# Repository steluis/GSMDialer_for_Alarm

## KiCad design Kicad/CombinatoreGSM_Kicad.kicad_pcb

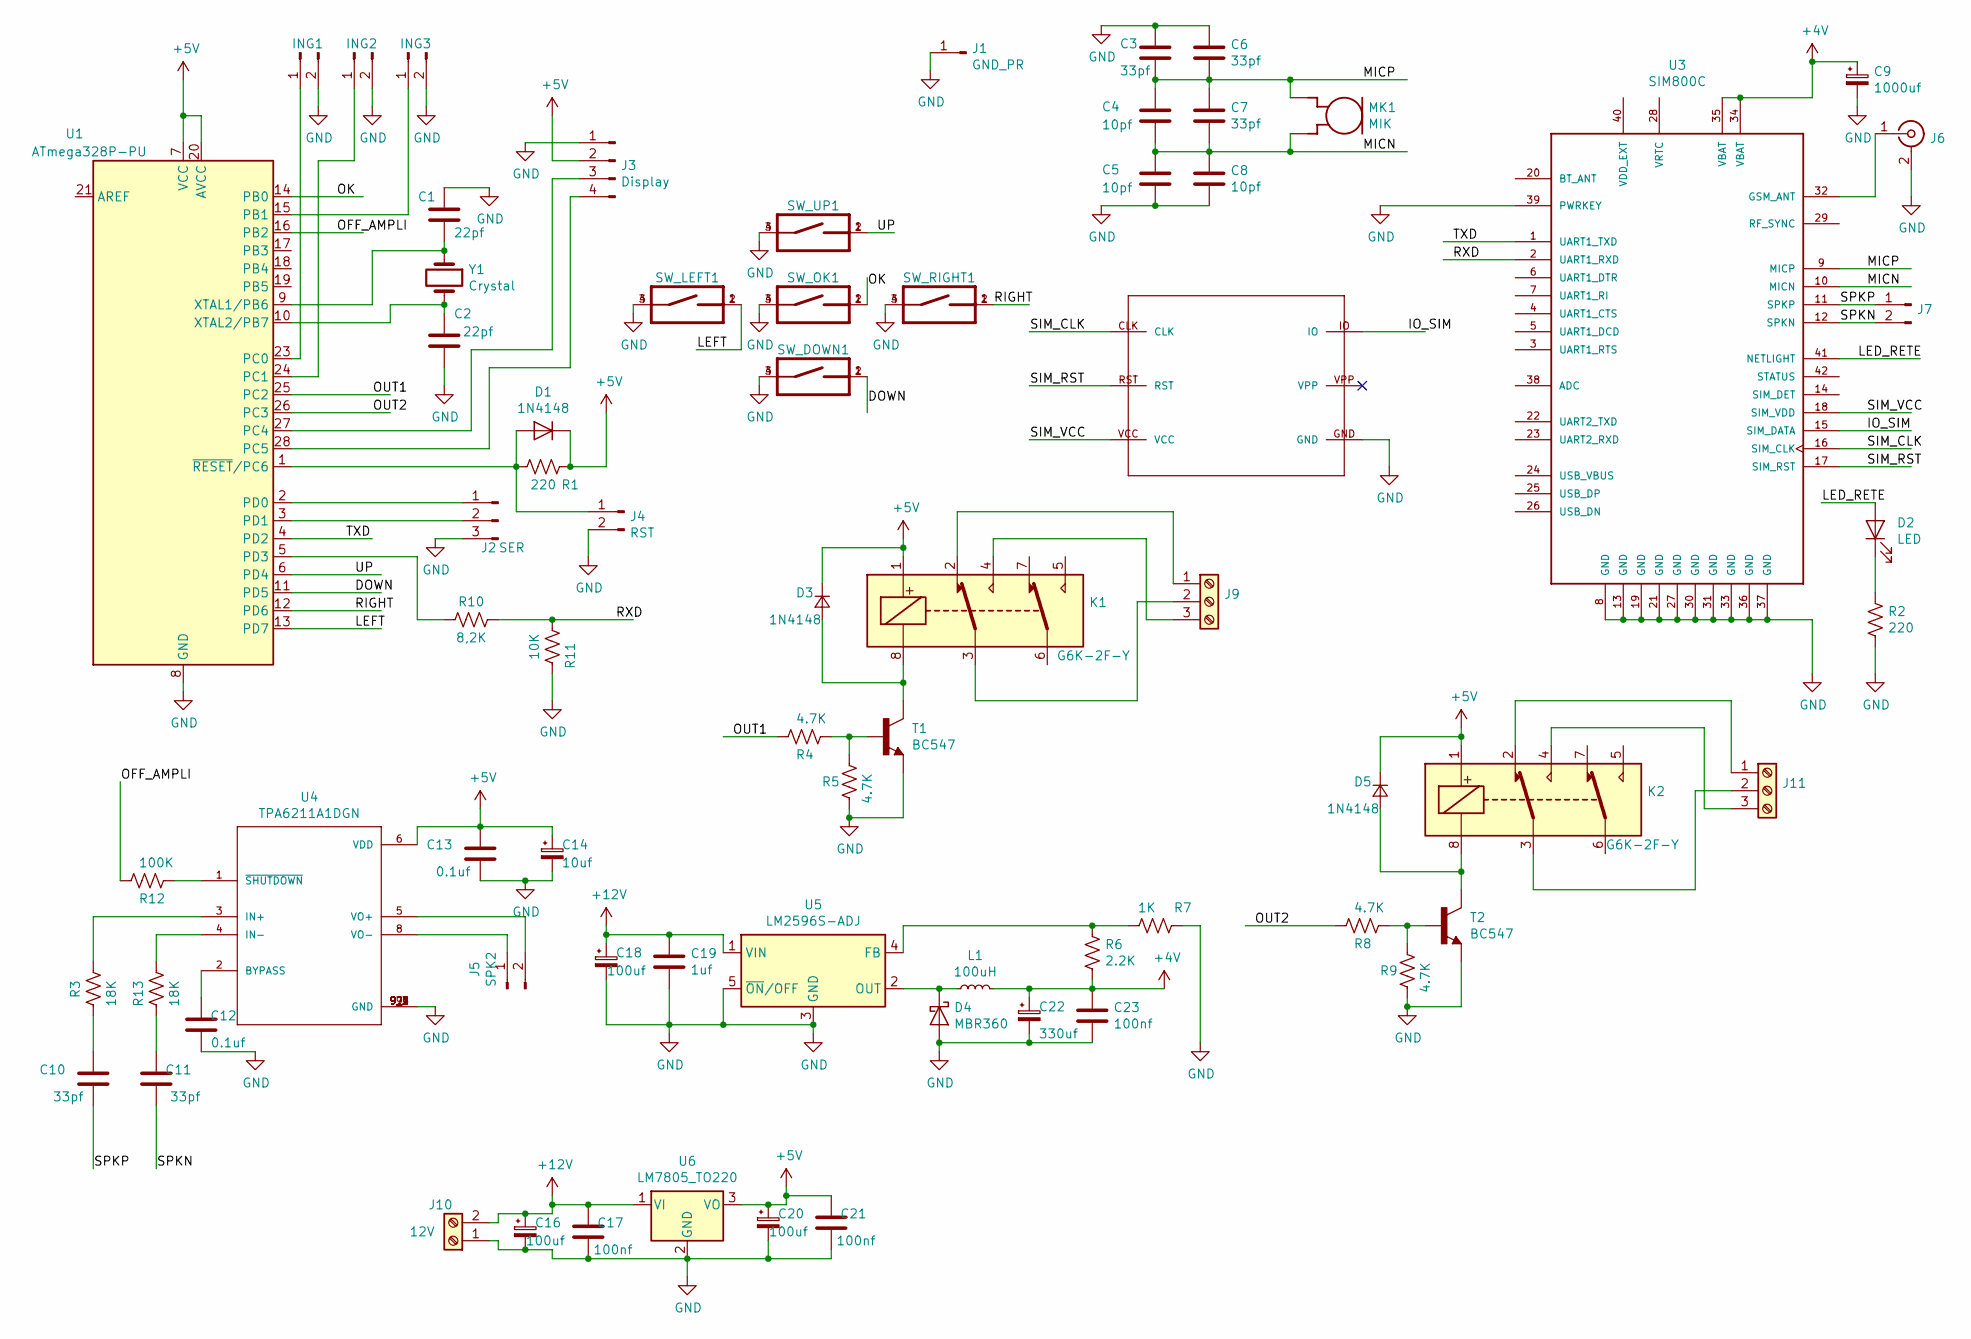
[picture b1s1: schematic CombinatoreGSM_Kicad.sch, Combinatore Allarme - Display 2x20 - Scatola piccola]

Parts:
C1, C2: 22pf; C_Disc_D3.0mm_W1.6mm_P2.50mm
C3, C6, C7, C10, C11: 33pf; C_0805_2012Metric_Pad1.15x1.40mm_HandSolder
C4, C5, C8: 10pf; C_0805_2012Metric_Pad1.15x1.40mm_HandSolder
C9: 1000uf; CP_Elec_10x10
C12, C13: 0.1uf; C_0805_2012Metric_Pad1.15x1.40mm_HandSolder
C14: 10uf; CP_Elec_6.3x5.9
C16, C18, C20: 100uf; CP_Elec_6.3x5.9
C17, C21, C23: 100nf; C_0805_2012Metric_Pad1.15x1.40mm_HandSolder
C19: 1uf; C_0805_2012Metric_Pad1.15x1.40mm_HandSolder
C22: 330uf; CP_Elec_6.3x5.9
D1, D3, D5: 1N4148; D_SOD-123
D2: LED; LED_D3.0mm
D4: MBR360; D_2010_5025Metric
ING1, ING2, ING3: TerminalBlock_4Ucon_1x02_P3.50mm_Horizontal
J1: GND_PR; PinHeader_1x01_P2.54mm_Vertical
J2: SER; PinHeader_1x03_P2.54mm_Vertical
J3: Display; PinHeader_1x04_P2.54mm_Horizontal
J4: RST; PinHeader_1x02_P2.54mm_Vertical
J5: SPK2; PinHeader_1x02_P2.54mm_Vertical
J6: U.FL_Hirose_U.FL-R-SMT-1_Vertical
J7: PinHeader_1x02_P2.54mm_Vertical
J9, J11: TerminalBlock_4Ucon_1x03_P3.50mm_Horizontal
J10: 12V; TerminalBlock_4Ucon_1x02_P3.50mm_Horizontal
K1, K2: G6K-2F-Y; Relay_DPDT_Omron_G6K-2F-Y
L1: 100uH; L_Axial_L7.0mm_D3.3mm_P12.70mm_Horizontal_Fastron_MICC
MK1: MIK; CUI_CMA-6542PF
R1, R2: 220; R_0805_2012Metric
R3, R13: 18K; R_0805_2012Metric
R4, R5, R8, R9: 4.7K; R_0805_2012Metric
R6: 2.2K; R_0805_2012Metric
R7: 1K; R_0805_2012Metric
R10: 8,2K; R_0805_2012Metric
R11: 10K; R_0805_2012Metric
R12: 100K; R_0805_2012Metric
SW_DOWN1: PULSANTE_DIP_SWITCH
SW_LEFT1: PULSANTE_DIP_SWITCH
SW_OK1: PULSANTE_DIP_SWITCH
SW_RIGHT1: PULSANTE_DIP_SWITCH
SW_UP1: PULSANTE_DIP_SWITCH
T1, T2: BC547; TO92
U1: ATmega328P-PU; DIP-28_W7.62mm
U2: NANO_SIM_CARD_HOLDER
U3: SIM800C; LCC110P1570X1760X250-42N
U4: TPA6211A1DGN; SOP65P490X110-9N
U5: LM2596S-ADJ; TO-263-5_TabPin3
U6: LM7805_TO220; TO-220-3_Horizontal_TabDown
Y1: Crystal; Crystal_HC49-4H_Vertical

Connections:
+4V: C9.1, C22.1, C23.1, L1.2, R6.2, U3.34 (VBAT), U3.35 (VBAT)
+5V: C13.2, C14.1, C20.1, C21.2, D1.1 (K), D3.1 (K), D5.1 (K), J3.2, K1.1, K2.1, R1.1, U1.7 (VCC), U1.20 (AVCC), U4.6 (VDD), U6.3 (VO); also elsewhere on the board
+12V: C16.1, C17.2, C18.1, C19.1, J10.2, U5.1 (VIN), U6.1 (VI)
/DOWN: SW_DOWN1.1 (2), SW_DOWN1.2, U1.11 (PD5)
/IO_SIM: U2.IO, U3.15 (SIM_DATA)
/LED_RETE: D2.2 (A), U3.41 (NETLIGHT)
/LEFT: SW_LEFT1.1 (2), SW_LEFT1.2, U1.13 (PD7)
/MICN: C4.2, C5.1, C7.2, C8.1, MK1.OUT, U3.10 (MICN)
/MICP: C3.2, C4.1, C6.2, C7.1, MK1.GND, U3.9 (MICP)
/OFF_AMPLI: R12.2, U1.16 (PB2)
/OK: SW_OK1.1 (2), SW_OK1.2, U1.14 (PB0)
/OUT1: R4.2, U1.25 (PC2)
/OUT2: R8.2, U1.26 (PC3)
/RIGHT: SW_RIGHT1.1 (2), SW_RIGHT1.2, U1.12 (PD6)
/RXD: R10.1, R11.2, U3.2 (UART1_RXD)
/SIM_CLK: U2.CLK, U3.16 (SIM_CLK)
/SIM_RST: U2.RST, U3.17 (SIM_RST)
/SIM_VCC: U2.VCC, U3.18 (SIM_VDD)
/SPKN: C11.1, J7.2, U3.12 (SPKN)
/SPKP: C10.1, J7.1, U3.11 (SPKP)
/TXD: U1.4 (PD2), U3.1 (UART1_TXD)
/UP: SW_UP1.1 (2), SW_UP1.2, U1.6 (PD4)
GND: C1.1, C2.2, C3.1, C5.2, C6.1, C8.2, C9.2, C12.1, C13.1, C14.2, C16.2, C17.1, C18.2, C19.2, C20.2, C21.1, C22.2, C23.2, D4.2 (A), ING1.2, ING2.2, ING3.2, J1.1, J2.3, J3.1, J4.2, J6.2 (Ext), J10.1, R2.2, R5.1, R7.1, R9.1, R11.1, SW_DOWN1.3 (1), SW_DOWN1.4 (1), SW_LEFT1.3 (1), SW_LEFT1.4 (1), SW_OK1.3 (1), SW_OK1.4 (1), SW_RIGHT1.3 (1), SW_RIGHT1.4 (1), SW_UP1.3 (1), SW_UP1.4 (1), T1.1 (E), T2.1 (E), U1.8 (GND), U1.22 (GND), U2.GND, U3.8 (GND), U3.13 (GND), U3.19 (GND), U3.21 (GND), U3.27 (GND), U3.30 (GND), U3.31 (GND), U3.33 (GND), U3.36 (GND), U3.37 (GND), U3.39 (PWRKEY), U4.7 (GND), U4.9 (GND), U4.9_1 (GND), U4.9_2 (GND), U4.9_3 (GND), U4.9_4 (GND), U4.9_5 (GND), U5.3 (GND), U5.5 (~ON~/OFF), U6.2 (GND); also elsewhere on the board
unnamed: C1.2, U1.9 (XTAL1/PB6), Y1.1
unnamed: C2.1, U1.10 (XTAL2/PB7), Y1.2
unnamed: C10.2, R3.1
unnamed: C11.2, R13.1
unnamed: C12.2, U4.2 (BYPASS)
unnamed: D1.2 (A), J4.1, R1.2, U1.1 (~RESET~/PC6)
unnamed: D2.1 (K), R2.1
unnamed: D3.2 (A), K1.8, T1.3 (C)
unnamed: D4.1 (K), L1.1, U5.2 (OUT)
unnamed: D5.2 (A), K2.8, T2.3 (C)
unnamed: ING1.1, U1.23 (PC0)
unnamed: ING2.1, U1.24 (PC1)
unnamed: ING3.1, U1.15 (PB1)
unnamed: J2.1, U1.2 (PD0)
unnamed: J2.2, U1.3 (PD1)
unnamed: J3.3, U1.27 (PC4)
unnamed: J3.4, U1.28 (PC5)
unnamed: J5.1, U4.8 (VO-)
unnamed: J5.2, U4.5 (VO+)
unnamed: J6.1 (In), U3.32 (GSM_ANT)
unnamed: J9.1, K1.2
unnamed: J9.2, K1.3
unnamed: J9.3, K1.4
unnamed: J11.1, K2.2
unnamed: J11.2, K2.3
unnamed: J11.3, K2.4
unnamed: R3.2, U4.3 (IN+)
unnamed: R4.1, R5.2, T1.2 (B)
unnamed: R6.1, R7.2, U5.4 (FB)
unnamed: R8.1, R9.2, T2.2 (B)
unnamed: R10.2, U1.5 (PD3)
unnamed: R12.1, U4.1 (~SHUTDOWN~)
unnamed: R13.2, U4.4 (IN-)

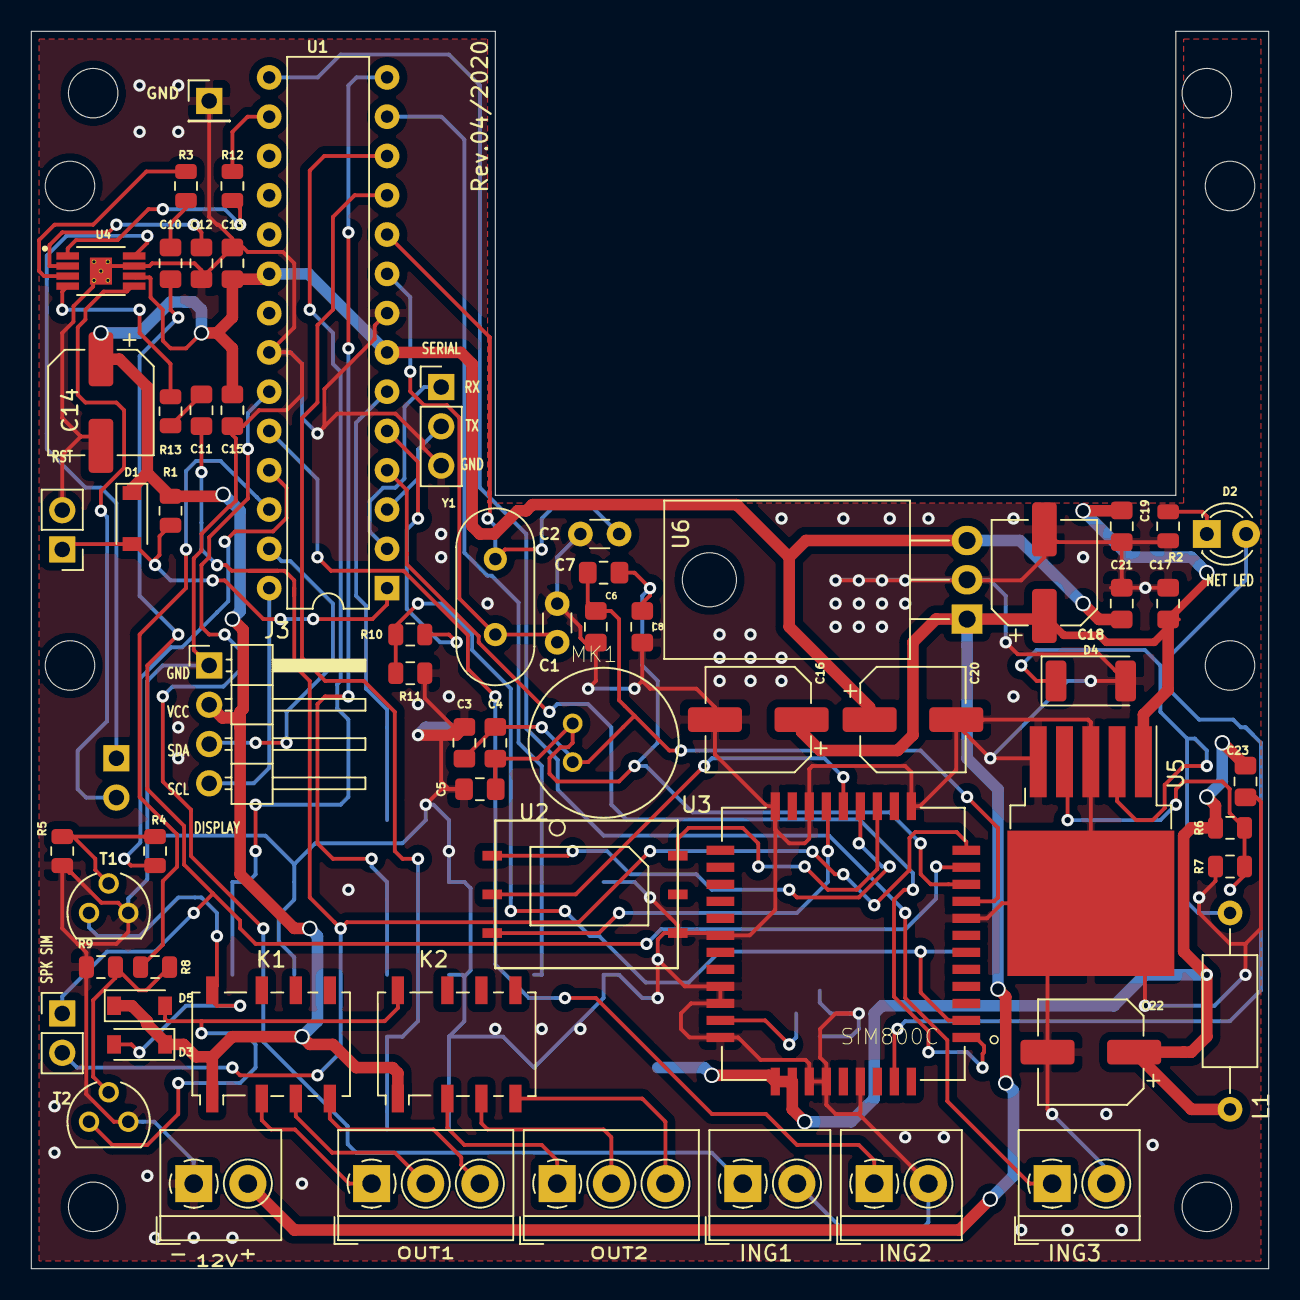
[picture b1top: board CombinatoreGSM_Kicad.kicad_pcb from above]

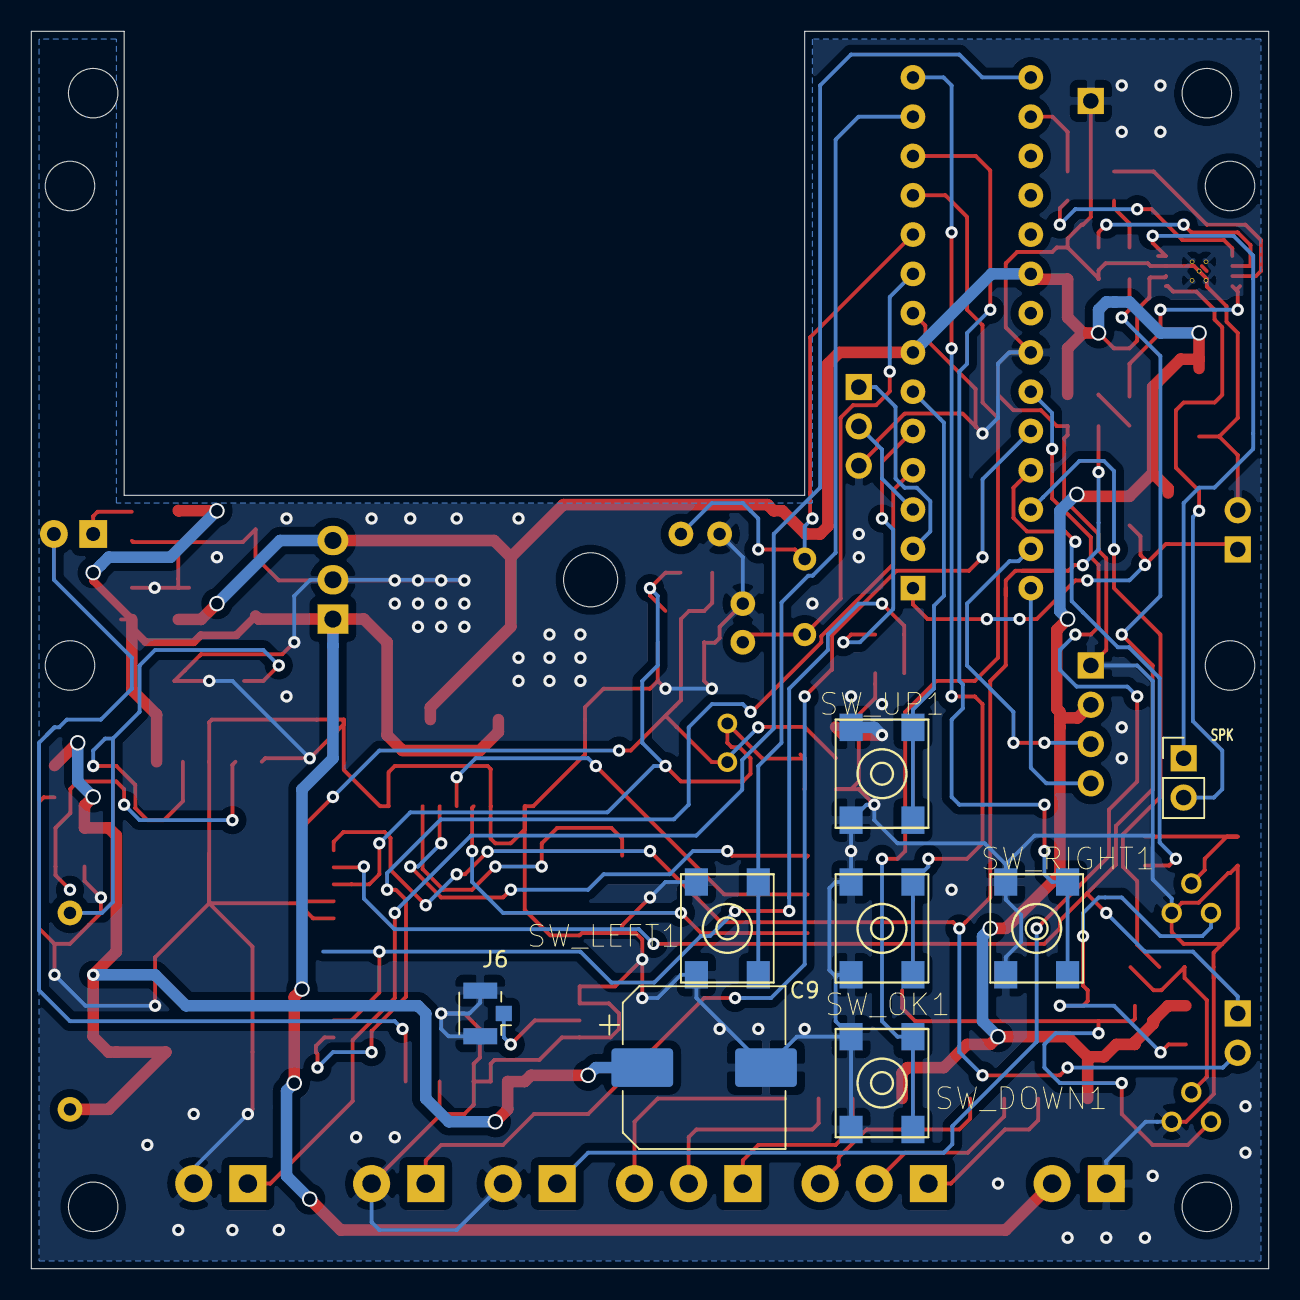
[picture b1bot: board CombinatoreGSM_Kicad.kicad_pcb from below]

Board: 2 copper layers, 80.0 x 80.0 mm, 79 parts (8 on the bottom side), 56 nets.

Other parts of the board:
., .#2, .#3: MountingHole_3.2mm_M3
C15: 1uf; C_0805_2012Metric_Pad1.15x1.40mm_HandSolder
_: MountingHole_3.2mm_M3
_#2, _#3, _#4: MountingHole_3.2mm_M3

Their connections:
+5V: C15.1; also elsewhere on the board
GND: C15.2; also elsewhere on the board
